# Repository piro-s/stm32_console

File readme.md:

## STM32 Console  
At the beginning it was a game console project on STM32, but then I found out 
about Anbernic devices. Now this is a debugging device for STM32F103Cx 
microcontrollers (STM32F103C6, C8, CB, maybe C4, but too little memory).  

---
The console has:  
+ display;  
+ buttons;  
+ temperature sensor LM75B;  
+ RTC module DS3231M;  
+ 4 LEDs;  
+ vibration motor;  
+ external speaker;  
+ radio module NRF24L01;  
+ bluetooth module JDY-23;  
+ interface converters: RS-232, RS-485 (with terminator 120 Ohm), USB-UART.  

---
The external connector gives access to connect:  
+ 4 digital inputs/outputs;  
+ 2 PWM outputs;  
+ 1 analog input (max 6V, if you need more, connect a resistor in series, see the scheme for details);  
+ SPI, I2C, UART;  
+ RS-232, RS-485.  

Pinout (IDC-26M):  
| Pin | Name          | Description                                                      |
|-----|---------------|------------------------------------------------------------------|
| 1   | 5V            | Output from TP5400                                               |
| 2   | Vdd           | From usb or for power input                                      |
| 3   | 3.3V          | Output from AMS1117                                              |
| 4   | 5V            | Output from TP5400                                               |
| 5   | Analog input  | Max 6V, or use resistor for increase voltage divider             |
| 6   | PWM2          | PWM output or GPIO PORTB.9, limited 1k Ohm                       |
| 7   | GPIO PORTA.12 | Limited 1k Ohm                                                   |
| 8   | PWM1          | PWM output or GPIO PORTB.8, limited 1k Ohm                       |
| 9   | GPIO PORTA.11 | Limited 1k Ohm                                                   |
| 10  | SPI CS        | To connect an external device or GPIO PORTB.12, limited 1k Ohm   |
| 11  | GPIO PORTA.10 | Limited 1k Ohm                                                   |
| 12  | SPI MOSI      |                                                                  |
| 13  | GPIO PORTA.9  | Limited 1k Ohm                                                   |
| 14  | SPI SCK       |                                                                  |
| 15  | SPI MISO      |                                                                  |
| 16  | Data+         | Noninverting Receiver Input A / Driver Output A (for MOXA Data-) |
| 17  | I2C SCL       |                                                                  |
| 18  | Data-         | Inverting Receiver Input B / Driver Output B (for MOXA Data+)    |
| 19  | I2C SDA       |                                                                  |
| 20  | GND           |                                                                  |
| 21  | UART RX       | Also connect to driver RS-485 and USB                            |
| 22  | UART TX       | Also connect to driver RS-485 and USB                            |
| 23  | RS-232 RX     |                                                                  |
| 24  | RS-232 TX     |                                                                  |
| 25  | GND           |                                                                  |
| 26  | GND           |                                                                  |

---
#### Scheme:  
[Scheme_v0.1](docs/game_pad_keyboard_v0.1.pdf)  

#### PCB:  

#### Gerber:  
Archive for production:  
[gerber_v0.1](https://github.com/piro-s/stm32_console/raw/master/gerber/game_pad_keyboard_v0.1.zip)

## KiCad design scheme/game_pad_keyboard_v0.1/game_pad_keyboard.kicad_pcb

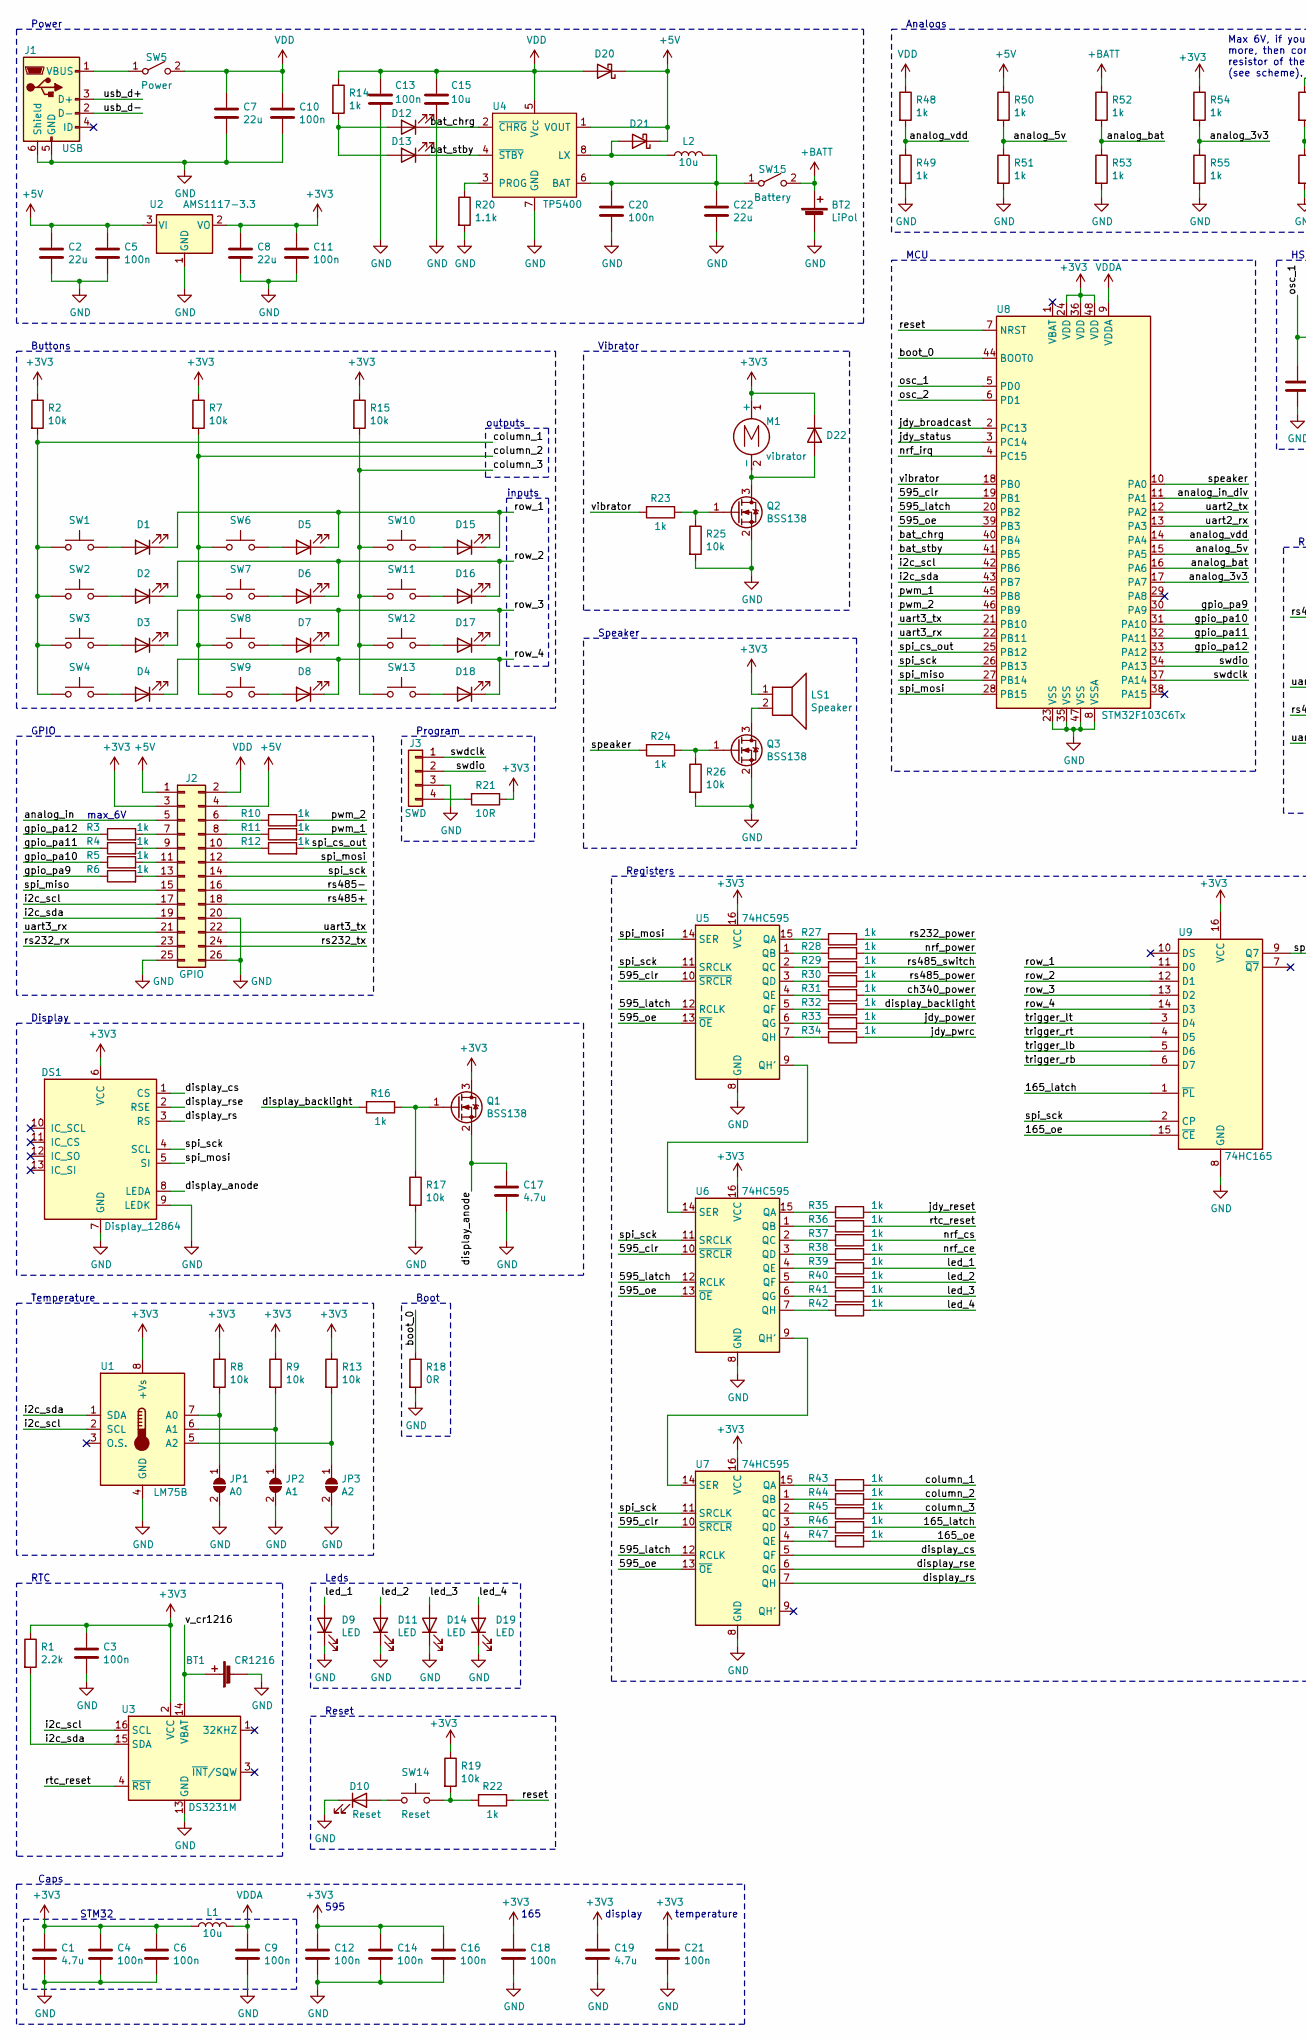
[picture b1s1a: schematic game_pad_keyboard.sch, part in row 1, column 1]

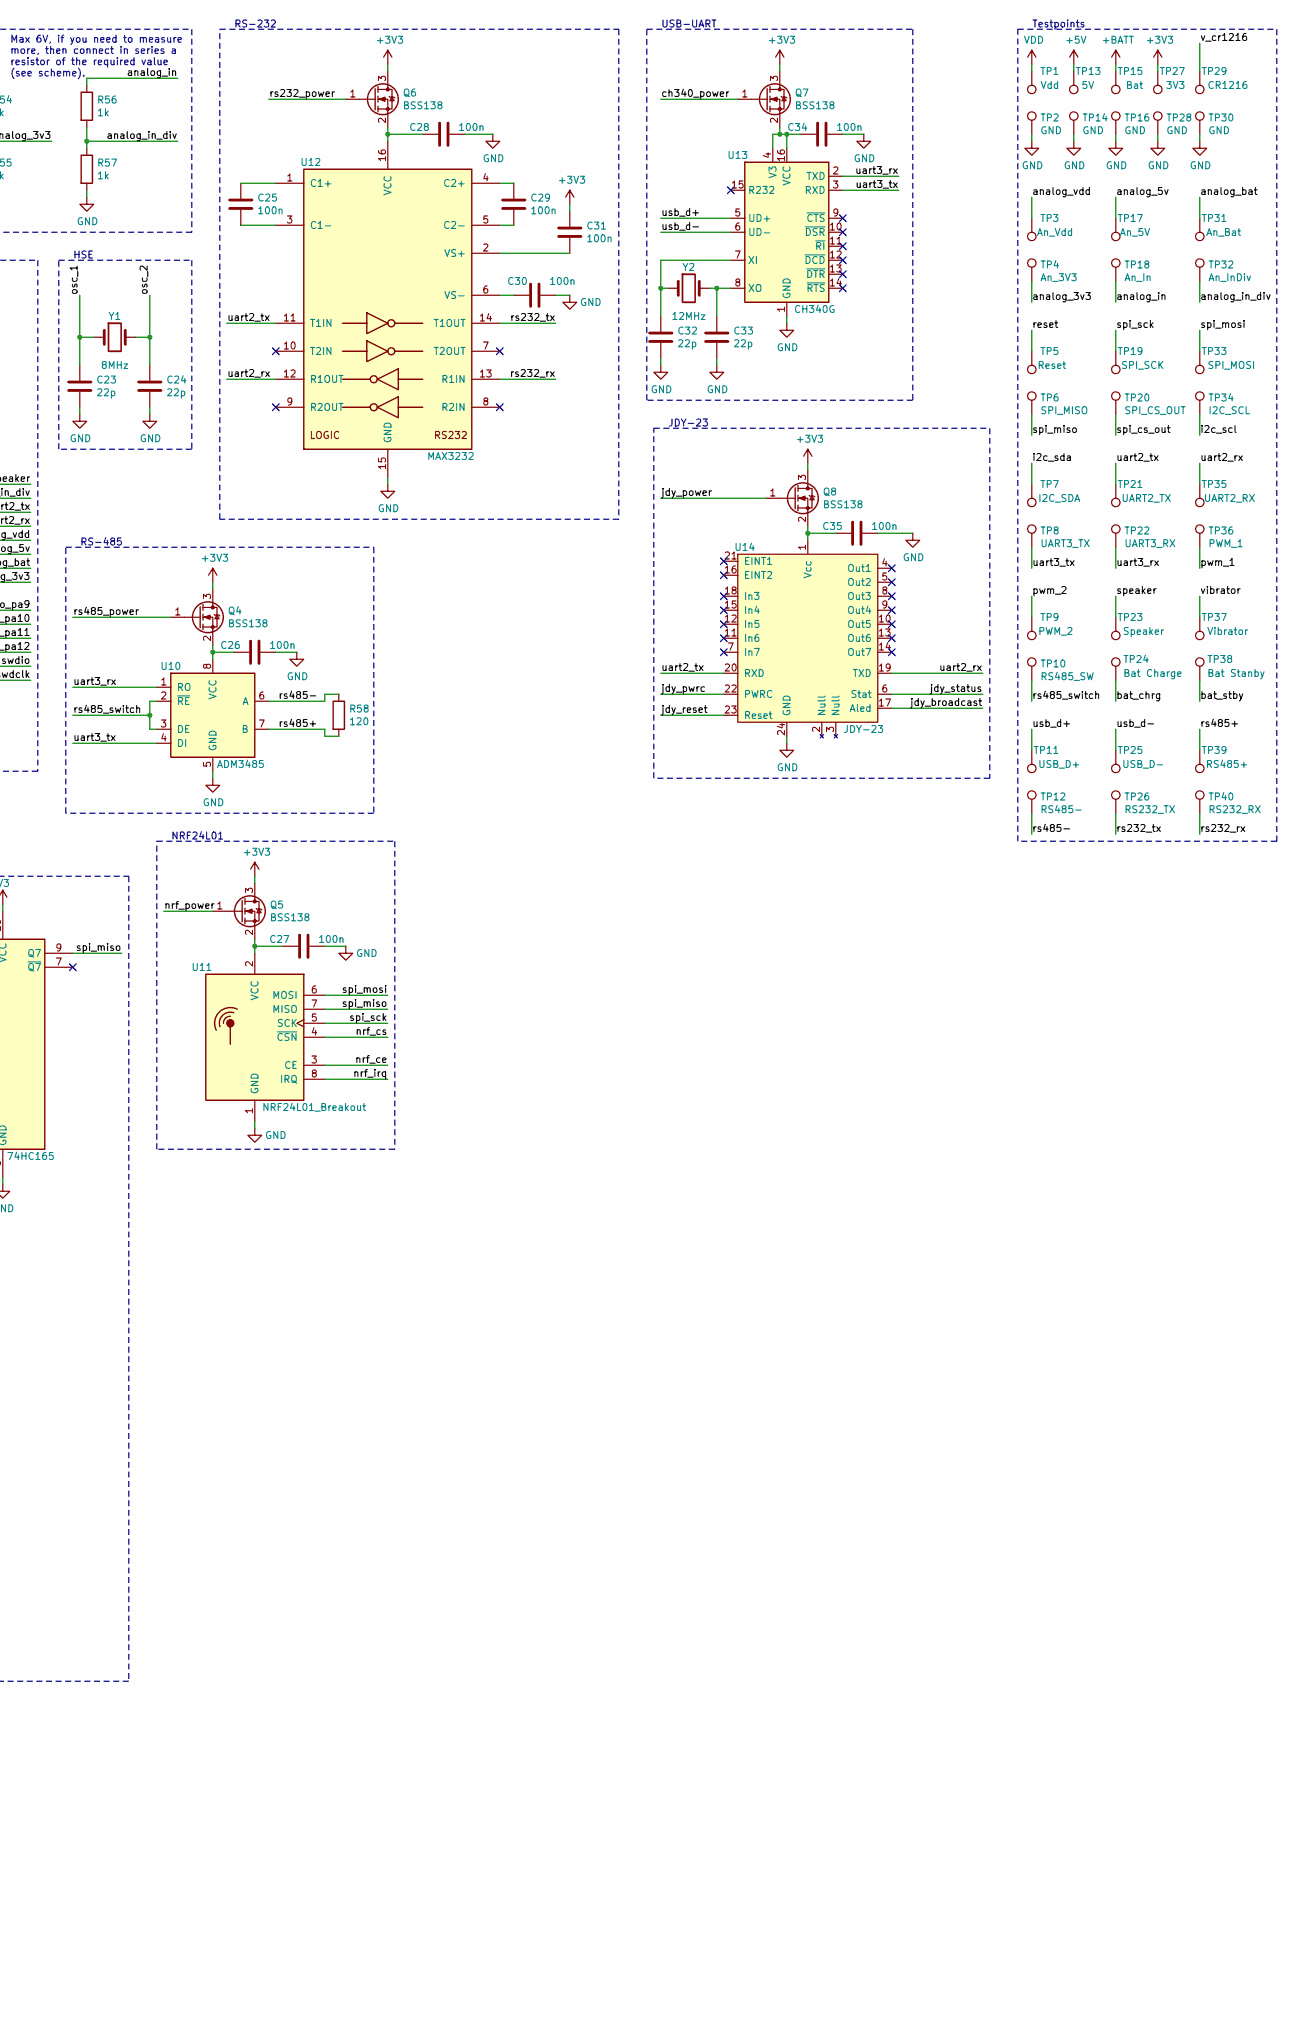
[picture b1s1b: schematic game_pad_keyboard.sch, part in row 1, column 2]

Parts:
BT1: CR1216; BatteryHolder_Keystone_3000_1x12mm
BT2: LiPol; PinSocket_1x02_P2.54mm_Vertical
C1, C17, C19: 4.7u; C_1206_3216Metric_Pad1.33x1.80mm_HandSolder
C2, C7, C8, C22: 22u; C_1206_3216Metric_Pad1.33x1.80mm_HandSolder
C3, C4, C5, C6, C9, C10, C11, C12, C13, C14, C16, C18, C20, C21, C25, C26, C27, C28, C29, C30, C31, C34, C35: 100n; C_0603_1608Metric_Pad1.08x0.95mm_HandSolder
C15: 10u; C_1206_3216Metric_Pad1.33x1.80mm_HandSolder
C23, C24, C32, C33: 22p; C_0603_1608Metric_Pad1.08x0.95mm_HandSolder
D1, D2, D3, D4, D5, D6, D7, D8, D12, D13, D15, D16, D17, D18: LED; LED_0603_1608Metric_Pad1.05x0.95mm_HandSolder
D9, D11, D14, D19: LED; LED_0805_2012Metric_Pad1.15x1.40mm_HandSolder
D10: Reset; LED_0603_1608Metric_Pad1.05x0.95mm_HandSolder
D20, D21: D_Schottky; D_0805_2012Metric_Pad1.15x1.40mm_HandSolder
D22: D; D_0603_1608Metric_Pad1.05x0.95mm_HandSolder
DS1: Display_12864
J1: USB; USB_Micro-B_Amphenol_10104110_Horizontal
J2: GPIO; IDC-Header_2x13_P2.54mm_Horizontal
J3: SWD; PinHeader_1x04_P2.54mm_Vertical
JP1: A0; SolderJumper-2_P1.3mm_Open_RoundedPad1.0x1.5mm
JP2: A1; SolderJumper-2_P1.3mm_Open_RoundedPad1.0x1.5mm
JP3: A2; SolderJumper-2_P1.3mm_Open_RoundedPad1.0x1.5mm
L1, L2: 10u; L_0805_2012Metric_Pad1.15x1.40mm_HandSolder
LS1: Speaker; PinSocket_1x02_P2.54mm_Vertical
M1: vibrator; PinHeader_1x02_P2.54mm_Vertical
Q1, Q2, Q3, Q4, Q5, Q6, Q7, Q8: BSS138; SOT-23
R1: 2.2k; R_0603_1608Metric_Pad0.98x0.95mm_HandSolder
R2, R7, R8, R9, R13, R15, R17, R19, R25, R26: 10k; R_0603_1608Metric_Pad0.98x0.95mm_HandSolder
R3, R4, R5, R6, R10, R11, R12, R14, R16, R22, R23, R24, R27, R28, R29, R30, R31, R32, R33, R34, R35, R36, R37, R38, R39, R40, R41, R42, R43, R44, R45, R46, R47, R48, R49, R50, R51, R52, R53, R54, R55, R56, R57: 1k; R_0603_1608Metric_Pad0.98x0.95mm_HandSolder
R18: 0R; R_0603_1608Metric_Pad0.98x0.95mm_HandSolder
R20: 1.1k; R_0603_1608Metric_Pad0.98x0.95mm_HandSolder
R21: 10R; R_0603_1608Metric_Pad0.98x0.95mm_HandSolder
R58: 120; R_0805_2012Metric_Pad1.20x1.40mm_HandSolder
SW1, SW2, SW3, SW4, SW6, SW7, SW8, SW9, SW10, SW11, SW12, SW13: SW_Push; SW_SPST_EVPBF
SW5: Power; SW_CuK_OS102011MA1QN1_SPDT_Angled
SW14: Reset; SW_PUSH_6mm
SW15: Battery; SW_CuK_OS102011MA1QN1_SPDT_Angled
TP1: Vdd; TestPoint_THTPad_1.0x1.0mm_Drill0.5mm
TP2, TP14, TP16, TP28, TP30: GND; TestPoint_THTPad_1.0x1.0mm_Drill0.5mm
TP3: An_Vdd; TestPoint_THTPad_1.0x1.0mm_Drill0.5mm
TP4: An_3V3; TestPoint_THTPad_1.0x1.0mm_Drill0.5mm
TP5: Reset; TestPoint_THTPad_1.0x1.0mm_Drill0.5mm
TP6: SPI_MISO; TestPoint_THTPad_1.0x1.0mm_Drill0.5mm
TP7: I2C_SDA; TestPoint_THTPad_1.0x1.0mm_Drill0.5mm
TP8: UART3_TX; TestPoint_THTPad_1.0x1.0mm_Drill0.5mm
TP9: PWM_2; TestPoint_THTPad_1.0x1.0mm_Drill0.5mm
TP10: RS485_SW; TestPoint_THTPad_1.0x1.0mm_Drill0.5mm
TP11: USB_D+; TestPoint_THTPad_1.0x1.0mm_Drill0.5mm
TP12: RS485-; TestPoint_THTPad_1.0x1.0mm_Drill0.5mm
TP13: 5V; TestPoint_THTPad_1.0x1.0mm_Drill0.5mm
TP15: Bat; TestPoint_THTPad_1.0x1.0mm_Drill0.5mm
TP17: An_5V; TestPoint_THTPad_1.0x1.0mm_Drill0.5mm
TP18: An_In; TestPoint_THTPad_1.0x1.0mm_Drill0.5mm
TP19: SPI_SCK; TestPoint_THTPad_1.0x1.0mm_Drill0.5mm
TP20: SPI_CS_OUT; TestPoint_THTPad_1.0x1.0mm_Drill0.5mm
TP21: UART2_TX; TestPoint_THTPad_1.0x1.0mm_Drill0.5mm
TP22: UART3_RX; TestPoint_THTPad_1.0x1.0mm_Drill0.5mm
TP23: Speaker; TestPoint_THTPad_1.0x1.0mm_Drill0.5mm
TP24: Bat Charge; TestPoint_THTPad_1.0x1.0mm_Drill0.5mm
TP25: USB_D-; TestPoint_THTPad_1.0x1.0mm_Drill0.5mm
TP26: RS232_TX; TestPoint_THTPad_1.0x1.0mm_Drill0.5mm
TP27: 3V3; TestPoint_THTPad_1.0x1.0mm_Drill0.5mm
TP29: CR1216; TestPoint_THTPad_1.0x1.0mm_Drill0.5mm
TP31: An_Bat; TestPoint_THTPad_1.0x1.0mm_Drill0.5mm
TP32: An_InDiv; TestPoint_THTPad_1.0x1.0mm_Drill0.5mm
TP33: SPI_MOSI; TestPoint_THTPad_1.0x1.0mm_Drill0.5mm
TP34: I2C_SCL; TestPoint_THTPad_1.0x1.0mm_Drill0.5mm
TP35: UART2_RX; TestPoint_THTPad_1.0x1.0mm_Drill0.5mm
TP36: PWM_1; TestPoint_THTPad_1.0x1.0mm_Drill0.5mm
TP37: Vibrator; TestPoint_THTPad_1.0x1.0mm_Drill0.5mm
TP38: Bat Stanby; TestPoint_THTPad_1.0x1.0mm_Drill0.5mm
TP39: RS485+; TestPoint_THTPad_1.0x1.0mm_Drill0.5mm
TP40: RS232_RX; TestPoint_THTPad_1.0x1.0mm_Drill0.5mm
U1: LM75B; SOIC-8_3.9x4.9mm_P1.27mm
U2: AMS1117-3.3; SOT-223-3_TabPin2
U3: DS3231M; SOIC-16W_7.5x10.3mm_P1.27mm
U4: TP5400; SOP-8_3.76x4.96mm_P1.27mm
U5, U6, U7: 74HC595; SOIC-16_3.9x9.9mm_P1.27mm
U8: STM32F103C6Tx; LQFP-48_7x7mm_P0.5mm
U9: 74HC165; SOIC-16_3.9x9.9mm_P1.27mm
U10: ADM3485; SOIC-8_3.9x4.9mm_P1.27mm
U11: NRF24L01_Breakout; nRF24L01_Breakout
U12: MAX3232; SOIC-16_3.9x9.9mm_P1.27mm
U13: CH340G; SOIC-16_3.9x9.9mm_P1.27mm
U14: JDY-23
Y1: 8MHz; Crystal_SMD_HC49-SD
Y2: 12MHz; Crystal_SMD_HC49-SD

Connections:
+3V3: C1.1, C3.1, C4.1, C6.1, C8.1, C11.1, C12.1, C14.1, C16.1, C18.1, C19.1, C21.1, C31.1, D22.1 (K), DS1.6 (VCC), J2.3, L1.1, LS1.1, M1.1 (+), Q1.3 (D), Q4.3 (D), Q5.3 (D), Q6.3 (D), Q7.3 (D), Q8.3 (D), R1.1, R2.1, R7.1, R8.1, R9.1, R13.1, R15.1, R19.1, R21.1, R54.1, TP27.1, U1.8 (+Vs), U2.2 (VO), U3.2 (VCC), U5.16 (VCC), U6.16 (VCC), U7.16 (VCC), U8.24 (VDD), U8.36 (VDD), U8.48 (VDD), U9.16 (VCC)
+5V: C2.1, C5.1, D20.1 (K), D21.1 (K), J2.1, J2.4, R50.1, TP13.1, U2.3 (VI), U4.1 (VOUT)
+BATT: BT2.1 (+), R52.1, SW15.2 (B), TP15.1
/165_latch: R46.1, U9.1 (~PL)
/165_oe: R47.1, U9.15 (~CE)
/595_clr: U5.10 (~SRCLR), U6.10 (~SRCLR), U7.10 (~SRCLR), U8.19 (PB1)
/595_latch: U5.12 (RCLK), U6.12 (RCLK), U7.12 (RCLK), U8.20 (PB2)
/595_oe: U5.13 (~OE), U6.13 (~OE), U7.13 (~OE), U8.39 (PB3)
/analog_3v3: R54.2, R55.1, TP4.1, U8.17 (PA7)
/analog_5v: R50.2, R51.1, TP17.1, U8.15 (PA5)
/analog_bat: R52.2, R53.1, TP31.1, U8.16 (PA6)
/analog_in: J2.5, R56.1, TP18.1
/analog_in_div: R56.2, R57.1, TP32.1, U8.11 (PA1)
/analog_vdd: R48.2, R49.1, TP3.1, U8.14 (PA4)
/bat_chrg: D12.1 (K), TP24.1, U4.2 (~CHRG), U8.40 (PB4)
/bat_stby: D13.1 (K), TP38.1, U4.4 (~STBY), U8.41 (PB5)
/boot_0: R18.1, U8.44 (BOOT0)
/ch340_power: Q7.1 (G), R31.1
/column_1: R2.2, R43.1, SW1.1, SW2.1, SW3.1, SW4.1
/column_2: R7.2, R44.1, SW6.1, SW7.1, SW8.1, SW9.1
/column_3: R15.2, R45.1, SW10.1, SW11.1, SW12.1, SW13.1
/display_anode: C17.1, DS1.8 (LEDA), Q1.2 (S)
/display_backlight: R16.2, R32.1
/display_cs: DS1.1 (CS), U7.5 (QF)
/display_rs: DS1.3 (RS), U7.7 (QH)
/display_rse: DS1.2 (RSE), U7.6 (QG)
/gpio_pa9: R6.1, U8.30 (PA9)
/gpio_pa10: R5.1, U8.31 (PA10)
/gpio_pa11: R4.1, U8.32 (PA11)
/gpio_pa12: R3.1, U8.33 (PA12)
/i2c_scl: J2.17, TP34.1, U1.2 (SCL), U3.16 (SCL), U8.42 (PB6)
/i2c_sda: J2.19, R1.2, TP7.1, U1.1 (SDA), U3.15 (SDA), U8.43 (PB7)
/jdy_broadcast: U8.2 (PC13), U14.17 (Aled)
/jdy_power: Q8.1 (G), R33.1
/jdy_pwrc: R34.1, U14.22 (PWRC)
/jdy_reset: R35.1, U14.23 (Reset)
/jdy_status: U8.3 (PC14), U14.6 (Stat)
/led_1: D9.2 (A), R39.1
/led_2: D11.2 (A), R40.1
/led_3: D14.2 (A), R41.1
/led_4: D19.2 (A), R42.1
/nrf_ce: R38.1, U11.3 (CE)
/nrf_cs: R37.1, U11.4 (~CSN)
/nrf_irq: U8.4 (PC15), U11.8 (IRQ)
/nrf_power: Q5.1 (G), R28.1
/osc_1: C23.1, U8.5 (PD0), Y1.1
/osc_2: C24.1, U8.6 (PD1), Y1.2
/pwm_1: R11.2, TP36.1, U8.45 (PB8)
/pwm_2: R10.2, TP9.1, U8.46 (PB9)
/reset: R22.1, TP5.1, U8.7 (NRST)
/row_1: D1.1 (K), D5.1 (K), D15.1 (K), U9.11 (D0)
/row_2: D2.1 (K), D6.1 (K), D16.1 (K), U9.12 (D1)
/row_3: D3.1 (K), D7.1 (K), D17.1 (K), U9.13 (D2)
/row_4: D4.1 (K), D8.1 (K), D18.1 (K), U9.14 (D3)
/rs232_power: Q6.1 (G), R27.1
/rs232_rx: J2.23, TP40.1, U12.13 (R1IN)
/rs232_tx: J2.24, TP26.1, U12.14 (T1OUT)
/rs485+: J2.18, R58.2, TP39.1, U10.7 (B)
/rs485-: J2.16, R58.1, TP12.1, U10.6 (A)
/rs485_power: Q4.1 (G), R30.1
/rs485_switch: R29.1, TP10.1, U10.2 (~RE~), U10.3 (DE)
/rtc_reset: R36.1, U3.4 (~RST)
/speaker: R24.2, TP23.1, U8.10 (PA0)
/spi_cs_out: R12.2, TP20.1, U8.25 (PB12)
/spi_miso: J2.15, TP6.1, U8.27 (PB14), U9.9 (Q7), U11.7 (MISO)
/spi_mosi: DS1.5 (SI), J2.12, TP33.1, U5.14 (SER), U8.28 (PB15), U11.6 (MOSI)
/spi_sck: DS1.4 (SCL), J2.14, TP19.1, U5.11 (SRCLK), U6.11 (SRCLK), U7.11 (SRCLK), U8.26 (PB13), U9.2 (CP), U11.5 (SCK)
/swdclk: J3.1, U8.37 (PA14)
/swdio: J3.2, U8.34 (PA13)
/trigger_lb: U9.5 (D6)
/trigger_lt: U9.3 (D4)
/trigger_rb: U9.6 (D7)
/trigger_rt: U9.4 (D5)
/uart2_rx: TP35.1, U8.13 (PA3), U12.12 (R1OUT), U14.19 (TXD)
/uart2_tx: TP21.1, U8.12 (PA2), U12.11 (T1IN), U14.20 (RXD)
/uart3_rx: J2.21, TP22.1, U8.22 (PB11), U10.1 (RO), U13.2 (TXD)
/uart3_tx: J2.22, TP8.1, U8.21 (PB10), U10.4 (DI), U13.3 (RXD)
/usb_d+: J1.3 (D+), TP11.1, U13.5 (UD+)
/usb_d-: J1.2 (D-), TP25.1, U13.6 (UD-)
/v_cr1216: BT1.1 (+), TP29.1, U3.14 (VBAT)
/vibrator: R23.2, TP37.1, U8.18 (PB0)
GND: BT1.2 (-), BT2.2 (-), C1.2, C2.2, C3.2, C4.2, C5.2, C6.2, C7.2, C8.2, C9.2, C10.2, C11.2, C12.2, C13.2, C14.2, C15.2, C16.2, C17.2, C18.2, C19.2, C20.2, C21.2, C22.2, C23.2, C24.2, C26.1, C27.1, C28.1, C30.1, C32.2, C33.2, C34.1, C35.1, D9.1 (K), D10.1 (K), D11.1 (K), D14.1 (K), D19.1 (K), DS1.7 (GND), DS1.9 (LEDK), J1.5 (GND), J1.6 (Shield), J2.20, J2.25, J2.26, J3.3, JP1.2 (B), JP2.2 (B), JP3.2 (B), Q2.2 (S), Q3.2 (S), R17.2, R18.2, R20.2, R25.2, R26.2, R49.2, R51.2, R53.2, R55.2, R57.2, TP2.1, TP14.1, TP16.1, TP28.1, TP30.1, U1.4 (GND), U2.1 (GND), U3.5 (GND), U3.6 (GND), U3.7 (GND), U3.8 (GND), U3.9 (GND), U3.10 (GND), U3.11 (GND), U3.12 (GND), U3.13 (GND), U4.7 (GND), U5.8 (GND), U6.8 (GND), U7.8 (GND), U8.8 (VSSA), U8.23 (VSS), U8.35 (VSS), U8.47 (VSS), U9.8 (GND), U10.5 (GND), U11.1 (GND), U12.15 (GND), U13.1 (GND), U14.24 (GND)
unnamed: C20.1, C22.1, L2.2, SW15.1 (A), U4.6 (BAT)
unnamed: C25.1, U12.1 (C1+)
unnamed: C25.2, U12.3 (C1-)
unnamed: C26.2, Q4.2 (S), U10.8 (VCC)
unnamed: C27.2, Q5.2 (S), U11.2 (VCC)
unnamed: C28.2, Q6.2 (S), U12.16 (VCC)
unnamed: C29.1, U12.4 (C2+)
unnamed: C29.2, U12.5 (C2-)
unnamed: C30.2, U12.6 (VS-)
unnamed: C31.2, U12.2 (VS+)
unnamed: C32.1, U13.7 (XI), Y2.1
unnamed: C33.1, U13.8 (XO), Y2.2
unnamed: C34.2, Q7.2 (S), U13.4 (V3), U13.16 (VCC)
unnamed: C35.2, Q8.2 (S), U14.1 (Vcc)
unnamed: D1.2 (A), SW1.2
unnamed: D2.2 (A), SW2.2
unnamed: D3.2 (A), SW3.2
unnamed: D4.2 (A), SW4.2
unnamed: D5.2 (A), SW6.2
unnamed: D6.2 (A), SW7.2
unnamed: D7.2 (A), SW8.2
unnamed: D8.2 (A), SW9.2
unnamed: D10.2 (A), SW14.1
unnamed: D12.2 (A), D13.2 (A), R14.2
unnamed: D15.2 (A), SW10.2
unnamed: D16.2 (A), SW11.2
unnamed: D17.2 (A), SW12.2
unnamed: D18.2 (A), SW13.2
unnamed: D21.2 (A), L2.1, U4.8 (LX)
unnamed: D22.2 (A), M1.2 (-), Q2.3 (D)
unnamed: J1.1 (VBUS), SW5.1 (A)
unnamed: J2.6, R10.1
unnamed: J2.7, R3.2
unnamed: J2.8, R11.1
unnamed: J2.9, R4.2
unnamed: J2.10, R12.1
unnamed: J2.11, R5.2
unnamed: J2.13, R6.2
unnamed: J3.4, R21.2
unnamed: JP1.1 (A), R8.2, U1.7 (A0)
unnamed: JP2.1 (A), R9.2, U1.6 (A1)
unnamed: JP3.1 (A), R13.2, U1.5 (A2)
unnamed: LS1.2, Q3.3 (D)
unnamed: Q1.1 (G), R16.1, R17.1
unnamed: Q2.1 (G), R23.1, R25.1
unnamed: Q3.1 (G), R24.1, R26.1
unnamed: R19.2, R22.2, SW14.2
unnamed: R20.1, U4.3 (PROG)
unnamed: R27.2, U5.15 (QA)
unnamed: R28.2, U5.1 (QB)
unnamed: R29.2, U5.2 (QC)
unnamed: R30.2, U5.3 (QD)
unnamed: R31.2, U5.4 (QE)
unnamed: R32.2, U5.5 (QF)
unnamed: R33.2, U5.6 (QG)
unnamed: R34.2, U5.7 (QH)
unnamed: R35.2, U6.15 (QA)
unnamed: R36.2, U6.1 (QB)
unnamed: R37.2, U6.2 (QC)
unnamed: R38.2, U6.3 (QD)
unnamed: R39.2, U6.4 (QE)
unnamed: R40.2, U6.5 (QF)
unnamed: R41.2, U6.6 (QG)
unnamed: R42.2, U6.7 (QH)
unnamed: R43.2, U7.15 (QA)
unnamed: R44.2, U7.1 (QB)
unnamed: R45.2, U7.2 (QC)
unnamed: R46.2, U7.3 (QD)
unnamed: R47.2, U7.4 (QE)
unnamed: U5.9 (QH'), U6.14 (SER)
unnamed: U6.9 (QH'), U7.14 (SER)
VDD: C7.1, C10.1, C13.1, C15.1, D20.2 (A), J2.2, R14.1, R48.1, SW5.2 (B), TP1.1, U4.5 (Vcc)
VDDA: C9.1, L1.2, U8.9 (VDDA)

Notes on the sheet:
inputs
outputs
Buttons
Vibrator
Display
Temperature
STM32
Power
HSE
Boot
Reset
Program
RS-232
RS-485
NRF24L01
JDY-23
RTC
display
Leds
Analogs
max_6V
temperature
595
Caps
USB-UART
Testpoints
Max 6V, if you need to measure more, then connect in series a resistor of the required value (see scheme).
GPIO
Registers
MCU
Speaker
165

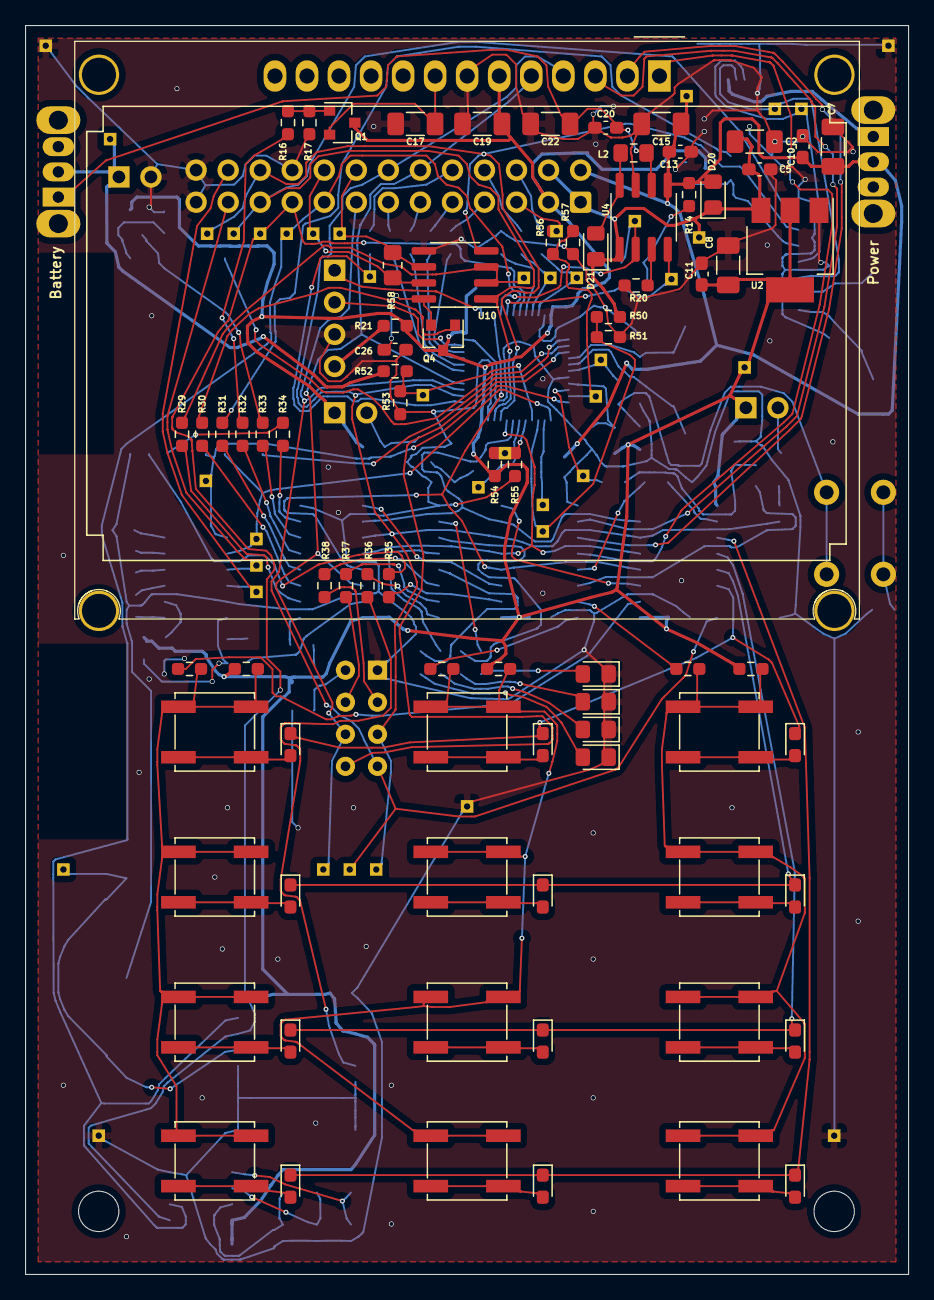
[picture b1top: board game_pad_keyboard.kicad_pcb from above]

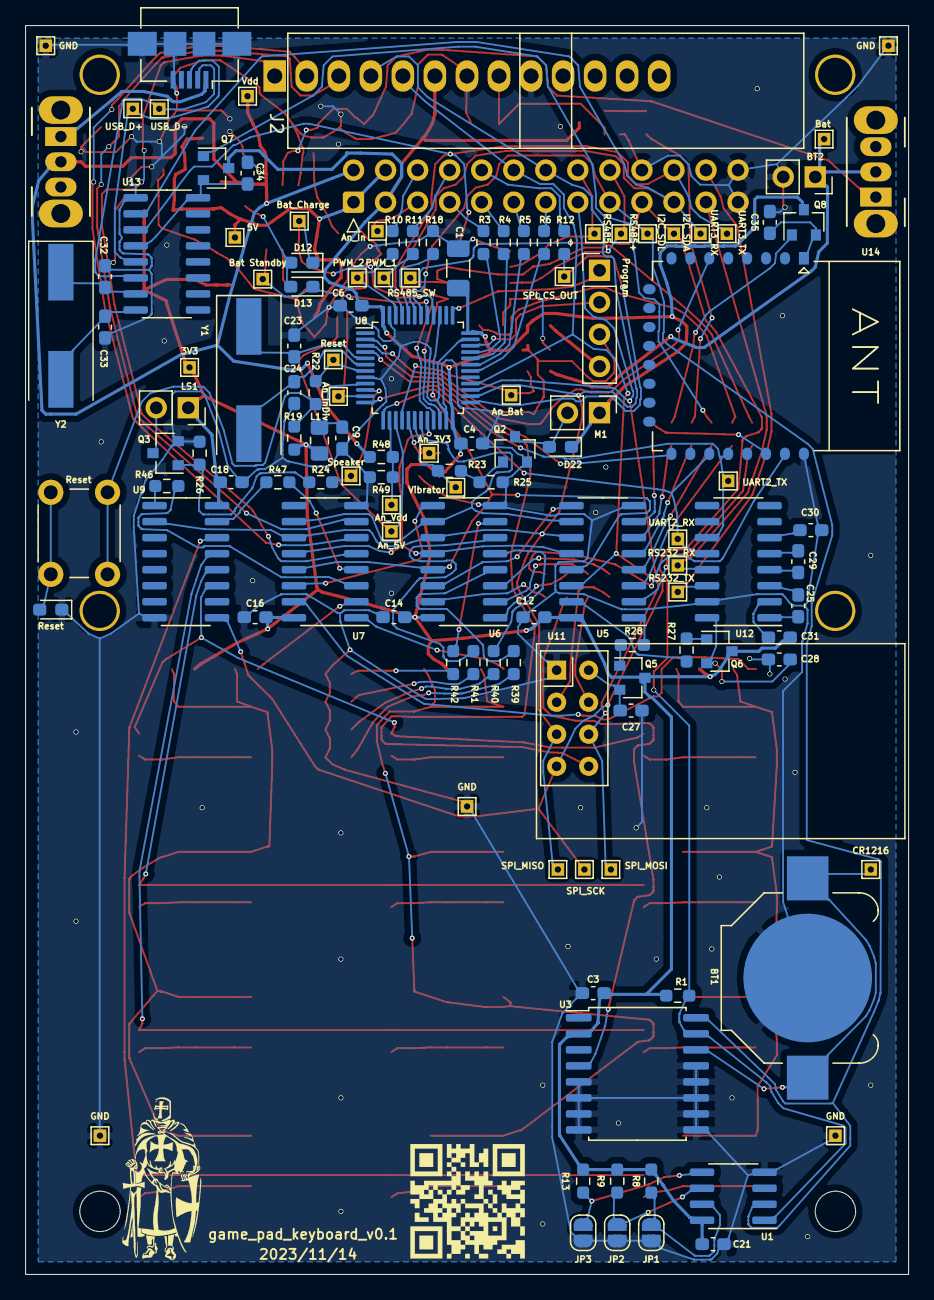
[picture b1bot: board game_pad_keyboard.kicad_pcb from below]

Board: 2 copper layers, 70.0 x 99.0 mm, 207 parts (127 on the bottom side), 151 nets.

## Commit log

2023-08-22 Initial
2023-08-22 fix: Gerber link
    Fixed link to gerber archieve.
2023-08-24 small: Pinout table
    Pinout description changed to pinout table.
2023-11-16 fix: Caps location
    Location of the capacitors has changed; they are
    now located after the transistors.
2023-11-16 new: Gerber file
    Add gerber with fix caps.
